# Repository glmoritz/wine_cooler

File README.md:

# wine_cooler
UPDATE: The hardware is working using this PID script -> https://github.com/glmoritz/tasmota_berry_pid

Control board replacement for an Electrolux Wine Cooler (https://loja.electrolux.com.br/adega-elctrolux--8-garrafas-1-porta-preta-acabamento-em-aluminio---acb08-/p?idsku=310118741&amp;utm_source=google&amp;utm_campaign=googlepla&amp;utm_medium=shopping&amp;gclid=CjwKCAjwl6OiBhA2EiwAuUwWZblqWcRMnEFmYsLsG8LWJ7mZvVhUz-GGubBmveTbVgpU_DQ_GiCKHBoC1JoQAvD_BwE)

The original control board for this wine cooler is a SH14387 board which is known to present failures during its lifespan. So, instead of ordering a new one for my broken wine cooler I decided to build my own control board using cheap aliexpress components.

The controller will be based on ESP32 Devboard C. This way I can run Tasmota in Thermostat mode and set/monitor all Cooler parameters using MQTT. Tasmota seamslessy integrates with Home Assistant, this way I will have very little work in firmware programming (just recompiling and configuring Tasmota with the correct parameters and then adding the device to Home Assistant).

Tasmota thermostat is very capable. It uses a mixed on/off PID strategy which seems to work well. Time will tell...

Board features:

- The board expects a 12V@6A input, which can be provided by a simple COTS power source.

- Controlled 12V 5A output for driving the peltier board.

- 2x Controlled 12V 200mA output for driving the cold/hot peltier fans.

- 10k NTC input for reading the built in Cooler NTC 

- DS1820 input (https://pt.aliexpress.com/item/4000895660165.html?spm=a2g0o.productlist.main.13.715dCEOXCEOXKd&algo_pvid=4737a506-6fa5-4de9-a575-1d5200c734fe&aem_p4p_detail=202304260539214864307083257520000789679&algo_exp_id=4737a506-6fa5-4de9-a575-1d5200c734fe-6&pdp_npi=3%40dis%21USD%210.94%210.85%21%21%21%21%21%40211bf3f716825127612216301d0789%2110000010464721123%21sea%21BR%21141474435&curPageLogUid=qv3l3xPca3AL&ad_pvid=202304260539214864307083257520000789679_7&ad_pvid=202304260539214864307083257520000789679_7)

This will be the Thermostat feedback sensor. The built in sensor is installed directly on peltier cell which is always colder than the cooler interior. I am planning to install the DS1820 nearer to the bottles to have a more precise temperature control.

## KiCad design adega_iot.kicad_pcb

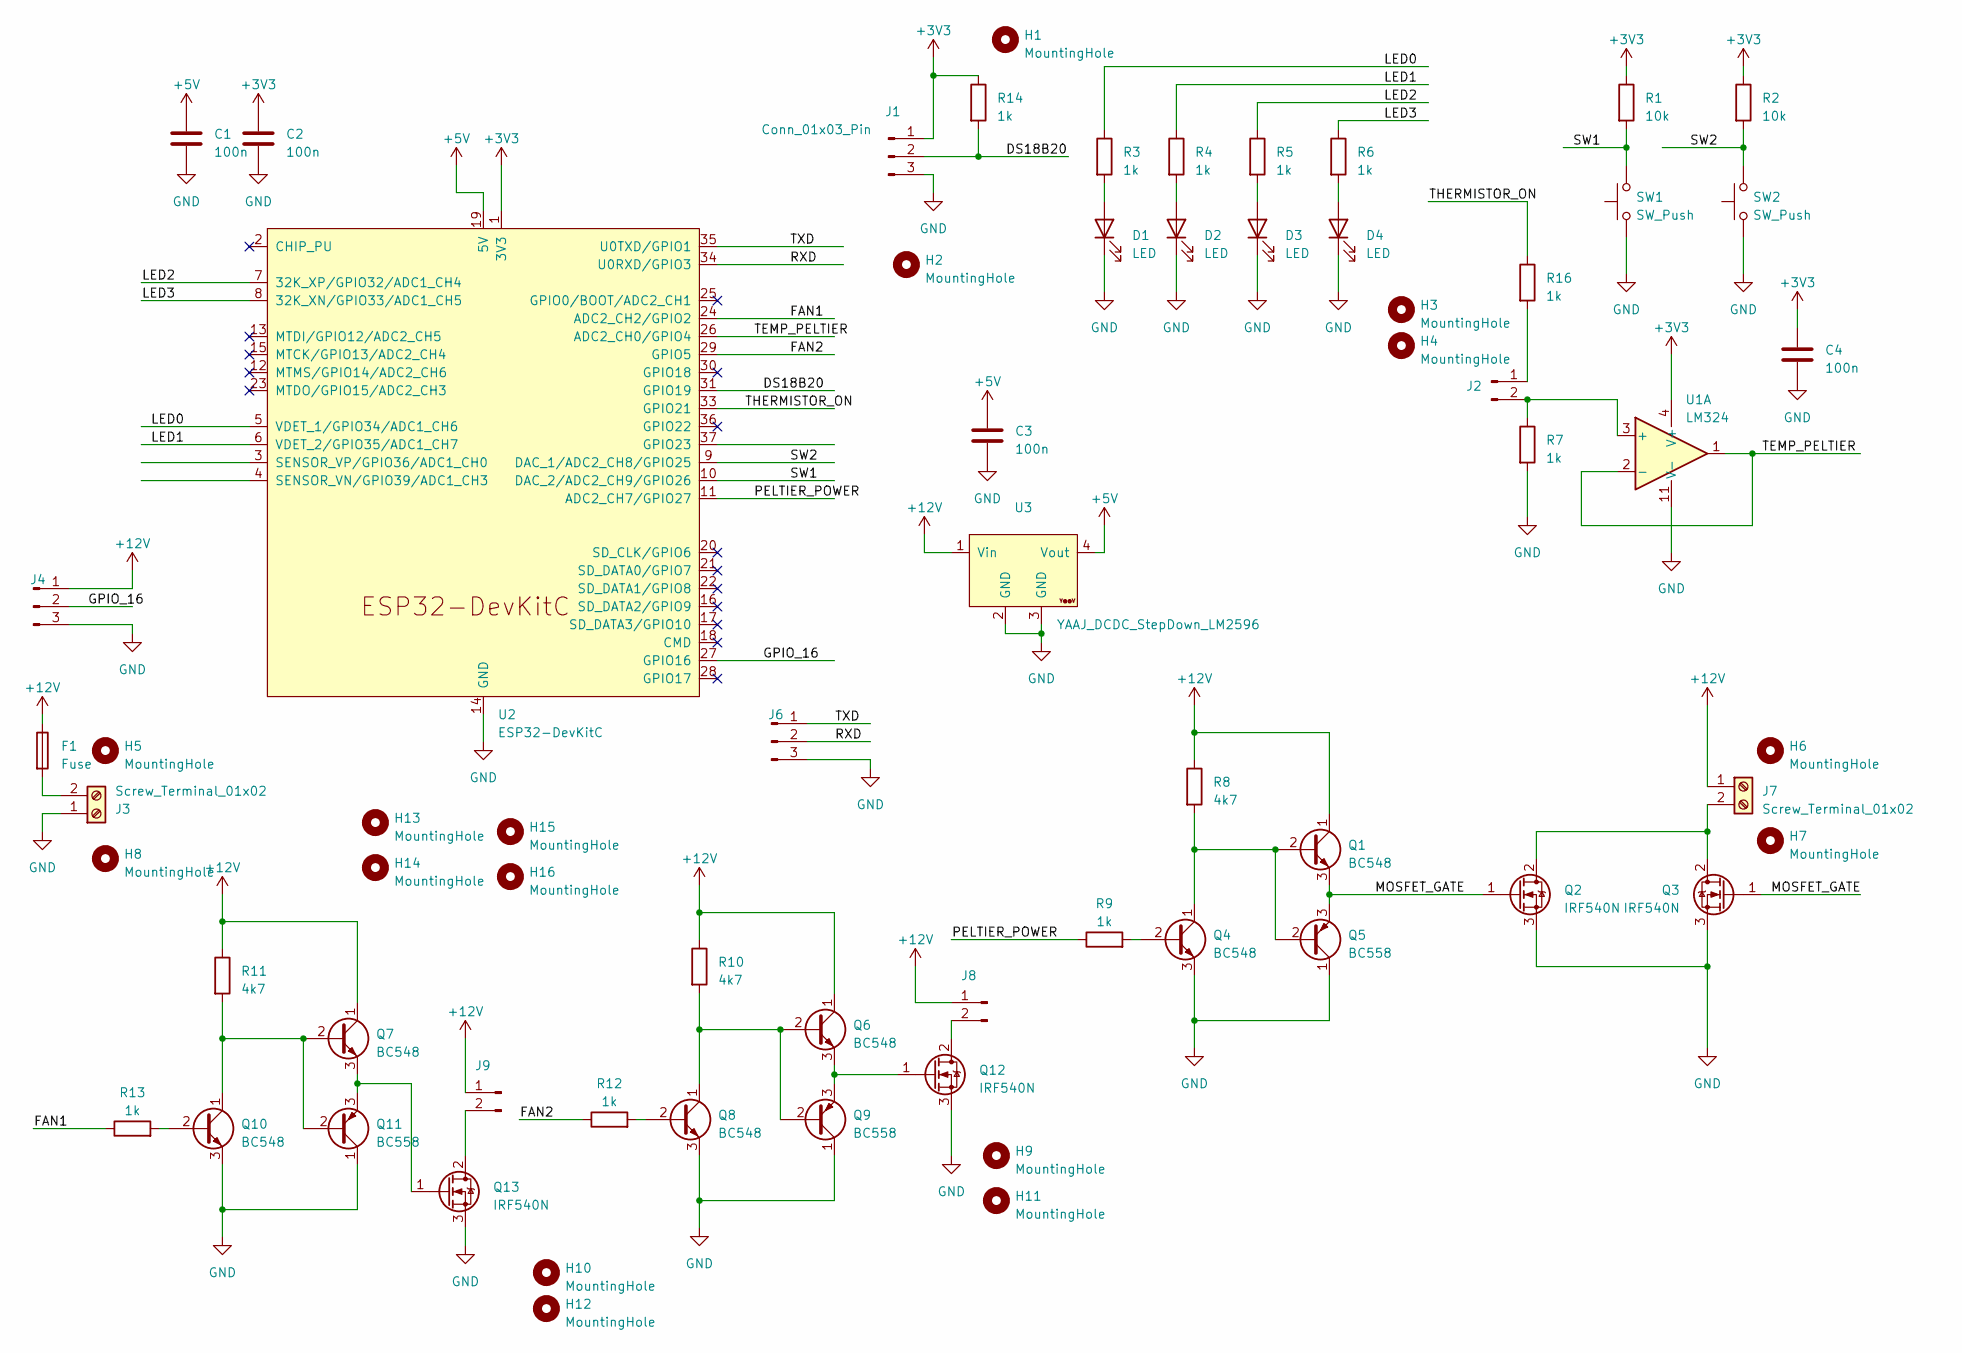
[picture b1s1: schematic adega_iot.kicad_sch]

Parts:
C1, C2, C3, C4: 100n; C_Disc_D7.5mm_W4.4mm_P5.00mm
D1, D2, D3, D4: LED; LED_D3.0mm
F1: Fuse; Metaltex_fuse_holder
H1, H2, H3, H4, H5, H6, H7, H8, H9, H10, H11, H12: MountingHole; MountingHole_2mm
H13, H14, H15, H16: MountingHole; MountingHole_3.2mm_M3
J1, J4, J6: Conn_01x03_Pin; PinHeader_1x03_P2.54mm_Vertical
J2, J8, J9: Conn_01x02_Pin; PinHeader_1x02_P2.54mm_Vertical
J3, J7: Screw_Terminal_01x02; HANDSON_KF301-2P
Q1, Q4, Q6, Q7, Q8, Q10: BC548; TO-92_Inline_Wide
Q2, Q3, Q12, Q13: IRF540N; TO-220-3_Vertical
Q5, Q9, Q11: BC558; TO-92_Inline_Wide
R1, R2: 10k; R_Axial_DIN0204_L3.6mm_D1.6mm_P7.62mm_Horizontal
R3, R4, R5, R6, R7, R9, R12, R13, R14, R16: 1k; R_Axial_DIN0204_L3.6mm_D1.6mm_P7.62mm_Horizontal
R8, R10, R11: 4k7; R_Axial_DIN0204_L3.6mm_D1.6mm_P7.62mm_Horizontal
SW1, SW2: SW_Push; SW_PUSH_6mm_H7.3mm
U1: LM324; DIP-14_W7.62mm
U2: ESP32-DevKitC
U3: YAAJ_DCDC_StepDown_LM2596

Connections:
+3V3: C2.1, C4.1, J1.1, R1.1, R2.1, R14.1, U1.4 (V+), U2.1 (3V3)
+5V: C1.1, C3.1, U2.19 (5V), U3.4 (Vout)
+12V: F1.1, J4.1, J7.1, J8.1, J9.1, Q1.1 (C), Q6.1 (C), Q7.1 (C), R8.1, R10.1, R11.1, U3.1 (Vin)
/DS18B20: J1.2, R14.2, U2.31 (GPIO19)
/FAN1: R13.1, U2.24 (ADC2_CH2/GPIO2)
/FAN2: R12.1, U2.29 (GPIO5)
/GPIO_16: J4.2, U2.27 (GPIO16)
/LED0: R3.1, U2.5 (VDET_1/GPIO34/ADC1_CH6)
/LED1: R4.1, U2.6 (VDET_2/GPIO35/ADC1_CH7)
/LED2: R5.1, U2.7 (32K_XP/GPIO32/ADC1_CH4)
/LED3: R6.1, U2.8 (32K_XN/GPIO33/ADC1_CH5)
/MOSFET_GATE: Q1.3 (E), Q2.1 (G), Q3.1 (G), Q5.3 (E)
/PELTIER_POWER: R9.1, U2.11 (ADC2_CH7/GPIO27)
/RXD: J6.2, U2.34 (U0RXD/GPIO3)
/SW1: R1.2, SW1.2, U2.10 (DAC_2/ADC2_CH9/GPIO26)
/SW2: R2.2, SW2.2, U2.9 (DAC_1/ADC2_CH8/GPIO25)
/TEMP_PELTIER: U1.1, U1.2 (-), U2.26 (ADC2_CH0/GPIO4)
/THERMISTOR_ON: R16.1, U2.33 (GPIO21)
/TXD: J6.1, U2.35 (U0TXD/GPIO1)
GND: C1.2, C2.2, C3.2, C4.2, D1.1 (K), D2.1 (K), D3.1 (K), D4.1 (K), J1.3, J3.1, J4.3, J6.3, Q2.3 (S), Q3.3 (S), Q4.3 (E), Q5.1 (C), Q8.3 (E), Q9.1 (C), Q10.3 (E), Q11.1 (C), Q12.3 (S), Q13.3 (S), R7.2, SW1.1, SW2.1, U1.11 (V-), U2.14 (GND), U2.32 (GND), U2.38 (GND), U3.2 (GND), U3.3 (GND)
unnamed: D1.2 (A), R3.2
unnamed: D2.2 (A), R4.2
unnamed: D3.2 (A), R5.2
unnamed: D4.2 (A), R6.2
unnamed: J2.1, R16.2
unnamed: J2.2, R7.1, U1.3 (+)
unnamed: F1.2, J3.2
unnamed: J7.2, Q2.2 (D), Q3.2 (D)
unnamed: J8.2, Q12.2 (D)
unnamed: J9.2, Q13.2 (D)
unnamed: Q1.2 (B), Q4.1 (C), Q5.2 (B), R8.2
unnamed: Q4.2 (B), R9.2
unnamed: Q6.2 (B), Q8.1 (C), Q9.2 (B), R10.2
unnamed: Q8.2 (B), R12.2
unnamed: Q10.2 (B), R13.2
unnamed: Q7.2 (B), Q10.1 (C), Q11.2 (B), R11.2
unnamed: Q7.3 (E), Q11.3 (E), Q13.1 (G)
unnamed: Q6.3 (E), Q9.3 (E), Q12.1 (G)

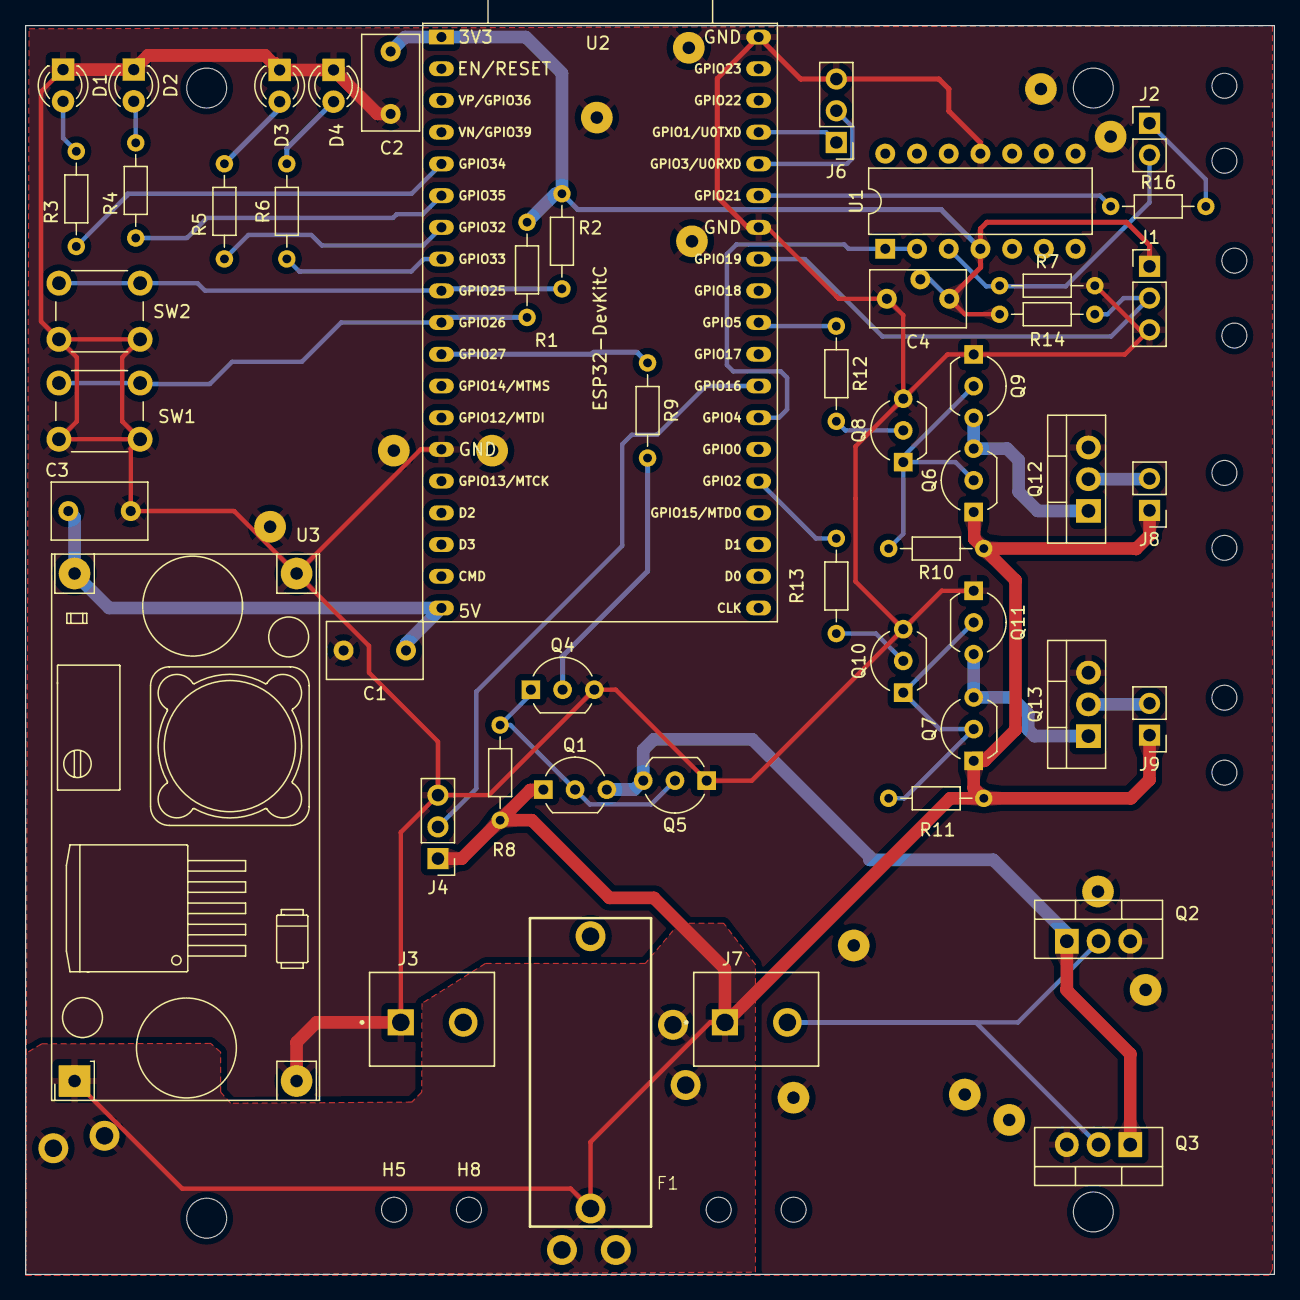
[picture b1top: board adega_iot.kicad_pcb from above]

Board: 2 copper layers, 100.0 x 100.0 mm, 66 parts (0 on the bottom side), 38 nets.

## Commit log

2023-04-26 First Version
2023-04-26 Added LM2596
2023-05-02 adding screw terminals
2023-05-03 Preliminary placement
2023-05-03 partial routing
2023-05-04 Routing Progress
2023-05-05 routing updates
2023-05-09 DRC and Teardrops
2023-05-10 Added a pullup to DS18B20
2023-05-12 Reset Button and NTC pullup
2023-05-23 Fabrication Outputs
2023-05-30 Added Thermistor on GPIO pin
2023-05-31 bug fixes
2023-05-31 more bug fixes
